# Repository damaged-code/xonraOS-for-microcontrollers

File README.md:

# xonraOS

**xonraOS** is a tiny phone-style operating system for an **ESP8266 (NodeMCU)** with a **128x64 OLED** and **two buttons**. It has a Home screen, a Wi-Fi clock, two games, Settings, and an **app Store** that downloads small JavaScript apps from your own server. Anyone can write an app in a few lines and publish it by copying a file.

> Status: made by a beginner as a learning project and tested on one NodeMCU (ESP-12E, CP2102) board. Issues and pull requests are welcome.

## What is in it

- **Home:** apps in a smooth scrolling grid.
- **Clock:** time and date from the internet (NTP), 12 or 24 hour.
- **Jump** and **Snake:** two games with high scores and sound.
- **Settings:** time format, brightness, seconds, animations, what the second button does, sound, and **Wi-Fi setup from your phone** (the board opens its own network and a web page).
- **Store:** browse category tiles, then app tiles, then an app's details. Hold to open a tile; on details, hold to get, update or remove the app. Installed apps appear on Home.
- **Apps are JavaScript** ([Elk](https://github.com/cesanta/elk) engine). They can draw, read the buttons and a knob, play beeps, fetch web pages and save a value. See [docs/APPS.md](docs/APPS.md).
- Apps are loaded into memory only while open, and many apps can be installed at once.

Sample apps in `server/apps/`: Counter, Stopwatch, Notes (scrolling text from your server), Knob Test, Bounce, Calculator.

The expanded catalog adds Countdown, Focus, Breathe, Dice, Reaction, Math Quiz, Scoreboard, Metronome, Morse, and Lane Dodge. See [the app pack guide](docs/APP-PACK.md) for controls and limitations. Firmware V2.0.3 lists up to 24 Store entries; up to eight apps can be installed at once.

V2.0.4 adds **Settings > Storage/Memory**: used/total and free app-file storage (LittleFS), live free RAM (heap), and installed app slots. Values are in KiB (1,024 bytes). Hold to refresh storage, tap to go back; D6 also goes back when configured as Back. Storage totals describe the filesystem partition, not the entire flash chip.

## Raspberry Pi

xonraOS also runs on a Raspberry Pi 3B with the same OLED and the same apps: see [pi/README.md](pi/README.md).

## Hardware

| Part | Connects to |
|---|---|
| ESP8266 NodeMCU (ESP-12E) | USB |
| 0.96" SSD1306 OLED, I2C address 0x3C | VCC to 3V3, GND to GND, SCL to D1, SDA to D2 |
| Main button | D7 and GND |
| Second button | D6 and GND |
| Buzzer (optional) | + to D8, - to GND |
| Potentiometer (optional) | left pin 3V3, middle pin A0, right pin GND |

Buttons use the internal pull-up, so no resistors are needed. A wiring diagram for a breadboard is in [docs/wiring.html](docs/wiring.html) (open it in a browser). An editable SVG copy for Figma or Inkscape is in [docs/wiring.svg](docs/wiring.svg).

## Controls

- **Main button (D7):** tap = next / action, hold 0.6 s = select, hold 1.5 s = back to Home.
- **Second button (D6):** set in Settings > D6 button: Off, Home, or Back (previous item, turn left, jump).

In the ESP8266 Store, a 1.5 s hold goes back one level (details → apps → categories → Home). From V2.0.7 / build 9, D6 in Back mode selects the previous tile or returns from details to the app grid; it stays in the Store during loading or on an empty catalog. D6 in Home mode still goes straight Home. Tiles page automatically as you tap through them. Details show the app's leading comment description, an image placeholder, and empty stars (no ratings are collected). Long tile names are shortened; open a tile to see its full catalog name. This layout is available in V2.0.6 / OTA build 8; the Pi Store retains its category list.

## Build and flash

1. Install the [Arduino IDE](https://www.arduino.cc/en/software) or Arduino CLI, and the **esp8266** board package (3.1.2 was used).
2. Install the libraries **Adafruit SSD1306**, **Adafruit GFX Library** (with Adafruit BusIO) and **elk** (2.2.0) from the Library Manager.
3. Copy `firmware/xonraOS/secrets.example.h` to `secrets.h` in the same folder and fill in your Wi-Fi name, password and app server address. (The ESP8266 supports 2.4 GHz Wi-Fi only.)
4. Edit `TIME_ZONE` near the top of `xonraOS.ino` if you are not in UTC+3.
5. Board: **NodeMCU 1.0 (ESP-12E Module)**. Compile and upload, for example:

```
arduino-cli compile --upload -p COM5 --fqbn esp8266:esp8266:nodemcuv2 firmware/xonraOS
```

If an upload fails with a write error, try again. If the board is not detected, install the CP210x USB driver.

## Update the firmware over Wi-Fi

Open **Settings > Firmware** on the board. It shows the installed build (for example `v2`) and the latest one on your app server. If a newer one exists, hold the main button to install it. The board downloads it, checks its signature, reboots and runs it. Do not unplug it while it says "Updating...".

Safety: the board only installs builds **signed with the maintainer's private key**; the matching public key is built into the firmware (`firmware/xonraOS/public.key`). A tampered or unsigned file is refused. Anyone with a USB cable can still flash any firmware.

For maintainers (publishing a release):
1. Raise `FW_VERSION` in `xonraOS.ino`.
2. Build: `arduino-cli compile --fqbn esp8266:esp8266:nodemcuv2 --output-dir build firmware/xonraOS`
3. Sign: `node tools/release-firmware.js build/xonraOS.ino.bin <path to private.key> release`
4. Copy `release/xonraos.bin` and `release/version.txt` to `firmware/` on your app server (so they are served at `/firmware/xonraos.bin` and `/firmware/version.txt`).

To run your own releases, make your own key pair (see the comments in `tools/release-firmware.js`), replace `public.key`, flash once over USB, and sign with your private key. Never commit `private.key`.

## Use the public app store

The quickest way to try the Store is the public one. In `secrets.h` set:

```
#define STORE_URL "http://35.174.38.92"
```

Browse the apps, with a live preview of each one, at **https://apps.xonra.cyou**. (The website uses `https://`; the board itself uses the plain `http://` address above because it cannot do `https://`.)

It serves whatever is in `server/` on the `main` branch of this repository (refreshed about every 10 minutes), so the apps there are the ones you see in the Store. To add an app, open a pull request that adds `server/apps/<id>.js` and a line in `server/manifest.txt`. Apps are reviewed before they are merged. The store is plain `http://` (the board cannot use `https://`), so install only apps you trust. It is a small hobby server and may go away; you can always host your own (next section).

## Run your own app server

```
cd server
python -m http.server 8266
```

Use the computer's LAN address as `STORE_URL` in `secrets.h`. Details: [server/README.md](server/README.md).

## Write an app

```js
//Hello|1|Hello
let n = 0;
let draw = function() {
  ctext(8, 1, 'Hello');
  ctext(24, 3, str(n));
  ctext(54, 1, 'Tap = +1');
};
let tap = function() { n = n + 1; };
```

Save it as `server/apps/hello.js`, add `hello|Hello|1|Tools` to `server/manifest.txt`, and install it from the Store. Read [docs/APPS.md](docs/APPS.md) first: the script engine has some bugs that fail silently, and there is a test harness (`tools/harness.c`) to check your app on your computer.

## Repository layout

```
firmware/xonraOS/   the OS (Arduino sketch)  - GPL-3.0
server/               app server files and sample apps - MIT
hardware/             open board design (draft) - CERN-OHL-S-2.0
pi/                   Raspberry Pi 3B version (same apps) - GPL-3.0
tools/harness.c       test an app on your computer
docs/                 app guide and wiring diagram
```

## License and credits

- The firmware and tools are under the **GNU GPL v3** (`LICENSE`), because they include the [Elk](https://github.com/cesanta/elk) JavaScript engine by Cesanta (AGPL/GPL). The sample apps and server files in `server/` are under the **MIT** license (`server/LICENSE`), so you can license your own apps as you like.
- Built on [Elk](https://github.com/cesanta/elk), the [ESP8266 Arduino core](https://github.com/esp8266/Arduino), and Adafruit's SSD1306, GFX and BusIO libraries.

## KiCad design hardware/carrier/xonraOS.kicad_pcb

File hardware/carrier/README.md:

# xonraOS carrier board v0.3 (the low-cost version)

A 2-layer, 60 × 88 mm board with the same outline, screen, buttons and side wheel as the v0.2 board, so it fits the
printed case in `../case`. The difference: instead of a factory-assembled ESP8266 + USB circuit, a ready-made
**Wemos D1 mini** is soldered flat onto it. Every part is through-hole or has big pads, so you can **order the bare
board (no assembly fee) and solder it yourself**.

Checked with KiCad's design-rule check: **0 unconnected pins, 0 errors** (only cosmetic silkscreen warnings).

> **Status: not built yet.** Measure your D1 mini before ordering (see "Check before ordering").

## Cost (rough, November 2026)

| Item | Where | Approx. |
|---|---|---|
| Carrier PCB, 5 pcs (`production/xonraOS-gerbers.zip`) | JLCPCB, no assembly | $2–4 |
| Wemos D1 mini (ESP8266, CH340) | AliExpress | about 8 SAR |
| 1.8" ST7735 TFT 128×160, SPI, 8-pin | AliExpress | about 12–15 SAR |
| 2 × 12 × 12 × 4.3 mm tactile buttons, 5 × 5 mm buzzer, 220 Ω resistor | AliExpress | about 5 SAR |
| Flat 16 mm thumbwheel potentiometer 10k | AliExpress | about 3–5 SAR |
| Case (`../case`) | JLC3DP, same order as the PCB | about 40 SAR |

Shipping is the biggest unknown: order the PCB and the case together, and all the small parts in one AliExpress order.

## Order the board

JLCPCB → "Add gerber file" → `production/xonraOS-gerbers.zip`. 2 layers, 1.6 mm, any colour. **Leave "PCB Assembly" off.**

## Solder it

1. **D1 mini:** push its male pin header through the D1 mini and the carrier, then **slide the black plastic spacer
   off** so the D1 mini lies flat (the parts under it drop into the cutout). USB to the left board edge. Solder both sides, trim.
2. **Screen (J2):** pin 1 at the top = VCC, then GND, CS, RESET, A0/DC, SDA, SCK, LED.
3. **Buttons** SW1 (main, D3) and SW2 (second, D6), **R1** 220 Ω, **buzzer LS1** (+ pad marked), **wheel RV1**.
4. Trim all solder legs on the back to about 1.5 mm so the board sits on the case posts.
5. Flash `firmware/xonraOS_TFT` as usual over the D1 mini's USB. No firmware changes are needed.

## Circuit

| D1 mini pin | Goes to |
|---|---|
| D5, D7 | TFT SCK, SDA (MOSI) |
| D1, D2 | TFT CS, A0/DC |
| RST | TFT RESET |
| D3 | main button to GND |
| D6 | second button to GND |
| D8 | 220 Ω, then buzzer to GND |
| A0 | wheel wiper (wheel ends on 3V3 and GND) |
| 3V3, G | TFT VCC and LED, wheel, ground pour |

## Check before ordering

- **D1 mini pin position:** the footprint assumes the 3V3/5V pins sit 5.6 mm from the USB end (typical). Measure yours.
- **Parts under the D1 mini** must fit inside the cutout (16.4 mm wide).
- **TFT pin order** as above (common red module). If yours differs, change the J2 pads in `make_board.py`.
- **Buzzer and wheel footprints** are generic (`../pcb/xonraOS.pretty`): compare with the parts you buy.

## Rebuild

From Git Bash: `sh build.sh` (KiCad 10, Freerouting 2.5 + Java 25), then
`"<KiCad>\bin\python.exe" export_jlc.py`. The script `make_board.py` holds all parts and nets.

License: CERN-OHL-S-2.0

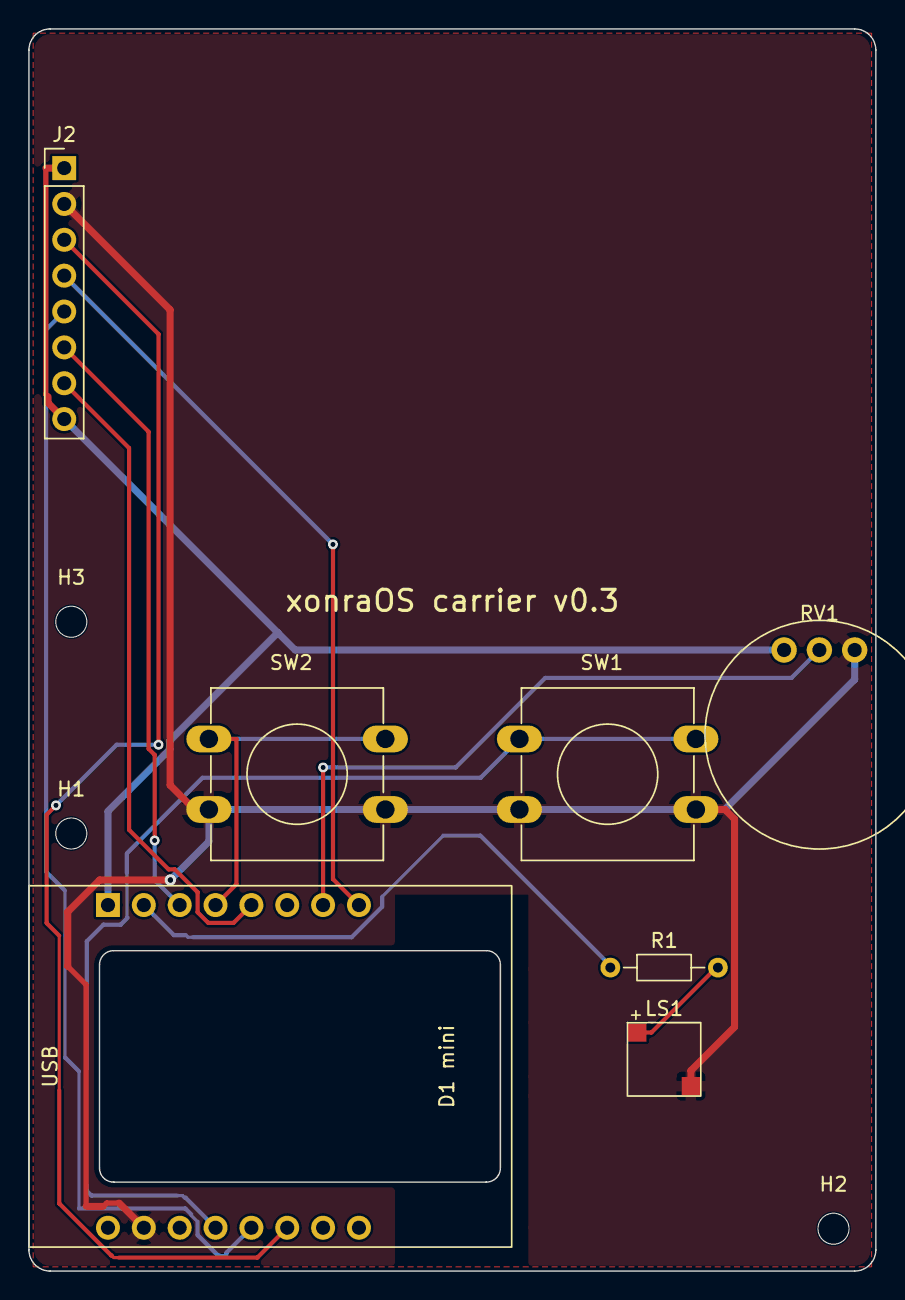
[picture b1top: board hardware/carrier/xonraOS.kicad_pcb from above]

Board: 2 copper layers, 60.0 x 88.0 mm, 10 parts (0 on the bottom side), 12 nets.

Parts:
H1, H2, H3: M2; MountingHole_2.2mm_M2
J2: TFT 1.8in ST7735; PinHeader_1x08_P2.54mm_Vertical
LS1: Buzzer 5x5; Buzzer_5x5_SMD
R1: 220R; R_Axial_DIN0204_L3.6mm_D1.6mm_P7.62mm_Horizontal
RV1: 10k thumbwheel; Thumbwheel_16mm
SW1: Main (D3); SW_PUSH-12mm
SW2: Second (D6); SW_PUSH-12mm
U1: Wemos D1 mini; WEMOS_D1_mini_flat

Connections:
+3V3: J2.1, J2.8, RV1.1, U1.3V3
BTN1: SW1.1, U1.D3
BTN2: SW2.1, U1.D6
BUZ: LS1.1, R1.2
BUZ_DRV: R1.1, U1.D8
GND: J2.2, LS1.2, RV1.3, SW1.2, SW2.2, U1.G
RST: J2.4, U1.RST
TFT_CS: J2.3, U1.D1
TFT_DC: J2.5, U1.D2
TFT_MOSI: J2.6, U1.D7
TFT_SCK: J2.7, U1.D5
WIPER: RV1.2, U1.A0

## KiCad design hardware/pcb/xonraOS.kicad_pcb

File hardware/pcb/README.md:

# xonraOS board v0.2 — KiCad PCB (1.8" colour TFT, portrait)

A 2-layer, 60 × 88 mm board that runs the TFT firmware (`firmware/xonraOS_TFT`) and fits the printed case in `../case`.
It was generated by scripts, routed with Freerouting, and checked with KiCad's design-rule check:
**0 unconnected pins, 0 electrical errors** (only cosmetic silkscreen warnings; see `drc-report.json`).

> **Status: not built yet.** The first boards may need small fixes. Before ordering, ask someone experienced to
> look at it (for example r/PrintedCircuitBoard), and check the parts below.

## Order it (JLCPCB)

Everything is in `production/`:

| File | Upload where |
|---|---|
| `xonraOS-gerbers.zip` | "Add gerber file". 2 layers, 1.6 mm, any colour (black looks premium). |
| `bom.csv` | "PCB Assembly" → BOM. Parts marked "by hand" are not assembled by JLCPCB. |
| `cpl.csv` | "PCB Assembly" → CPL (placement). |

In the assembly preview, **check the rotation of each part** (especially U1, U2, U3, the transistors and J1)
and rotate any that look wrong: the factory's part models do not always match KiCad's.

Solder these yourself afterwards (then trim all solder legs to about 1.5 mm so the board fits the thin case): the 1.8" TFT module (on J2, 8-pin header), the two low-profile 12 × 12 × 4.3 mm buttons (SW1, SW2),
the 5 × 5 mm buzzer (LS1) and the flat 16 mm thumbwheel potentiometer (RV1).

## What to check before ordering

- **TFT pin order (J2):** pin 1 at the top = VCC, then GND, CS, RESET, A0/DC, SDA, SCK, LED. This is the order on the
  common red 1.8" module; if yours differs, change the J2 pads in `make_board.py` and rebuild.
- **Buzzer (LS1) and thumbwheel (RV1)** use generic footprints in `xonraOS.pretty`: compare them with the datasheet of
  the parts you buy (pad positions, pin order: RV1 pin 1 = 3V3, 2 = wiper, 3 = GND).
- **LCSC part numbers** in `make_board.py` were picked from memory: confirm each is in stock at JLCPCB.

## Circuit summary

Pins match the TFT firmware: TFT SCK GPIO14, MOSI GPIO13, CS GPIO5, DC GPIO4, RESET = board reset; main button GPIO0
(also the flash button), second button GPIO12, buzzer GPIO15 through an S8050 transistor, thumbwheel on the ADC through a
220k/100k divider. USB-C → CH340C (powered at 3.3 V) with automatic reset/flash (two S8050s on DTR/RTS) → no buttons
needed to upload. AMS1117-3.3 regulator. The full net list is the `NETS` table in `make_board.py`.

## Rebuild it

Needs KiCad 10 and Java 25 + [Freerouting](https://github.com/freerouting/freerouting) 2.5.

```
"<KiCad>\bin\python.exe" make_board.py        # place parts, nets, outline, pours, keep-outs
"<KiCad>\bin\python.exe" route.py <java.exe> <freerouting.jar> 150
"<KiCad>\bin\kicad-cli.exe" pcb drc --refill-zones --save-board xonraOS.kicad_pcb
"<KiCad>\bin\python.exe" export_jlc.py        # production/ files
```

Part positions in `make_board.py` must stay in step with `../case/xonra-board-case.js` (buttons, wheel, USB-C, screen).

License: CERN-OHL-S-2.0 (see `../LICENSE`).

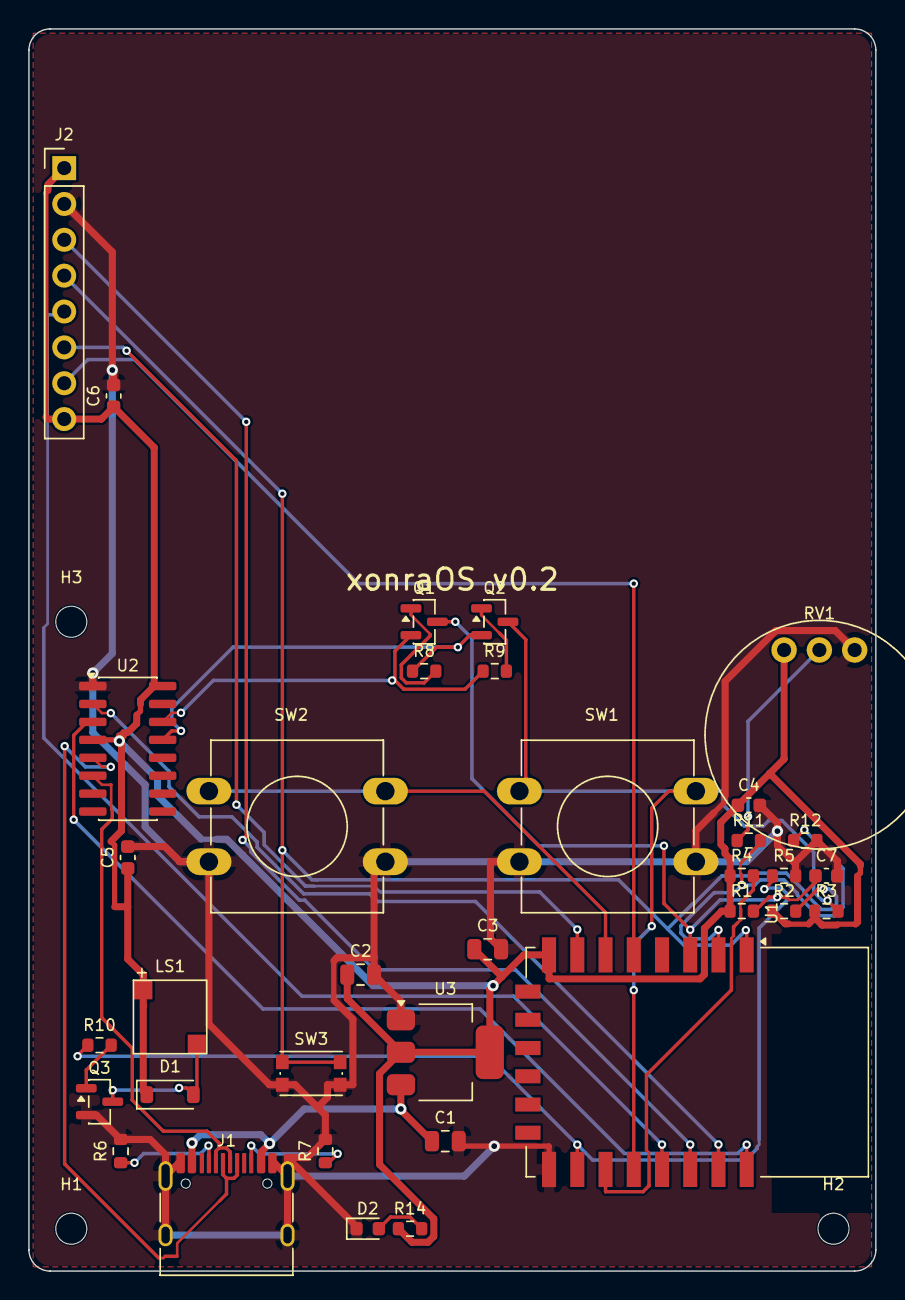
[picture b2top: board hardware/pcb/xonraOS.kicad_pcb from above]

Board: 2 copper layers, 60.0 x 88.0 mm, 38 parts (0 on the bottom side), 28 nets.

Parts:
C1, C2, C3: 10uF; C_0805_2012Metric
C4, C5, C6, C7: 100nF; C_0603_1608Metric
D1: 1N4148W; D_SOD-123
D2: LED; LED_0603_1608Metric
H1, H2, H3: M2; MountingHole_2.2mm_M2
J1: USB-C; USB_C_Receptacle_HRO_TYPE-C-31-M-12
J2: TFT 1.8in ST7735; PinHeader_1x08_P2.54mm_Vertical
LS1: Buzzer 5x5; Buzzer_5x5_SMD
Q1, Q2, Q3: S8050; SOT-23
R1, R2, R3, R4, R5, R8, R9: 10k; R_0603_1608Metric
R6, R7: 5.1k; R_0603_1608Metric
R10, R14: 1k; R_0603_1608Metric
R11: 220k; R_0603_1608Metric
R12: 100k; R_0603_1608Metric
RV1: 10k thumbwheel; Thumbwheel_16mm
SW1: Main (GPIO0); SW_PUSH-12mm
SW2: Second (GPIO12); SW_PUSH-12mm
SW3: Reset; SW_Push_1P1T_NO_CK_KMR2
U1: ESP-12F; ESP-12E
U2: CH340C; SOIC-16_3.9x9.9mm_P1.27mm
U3: AMS1117-3.3; SOT-223-3_TabPin2

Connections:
+3V3: C2.1, C3.1, C4.1, C5.1, C6.1, D1.1, J2.1, J2.8, LS1.1, R1.1, R2.1, R3.1, R4.1, R14.1, RV1.1, U1.8, U2.4, U2.16, U3.2
BTN2: SW2.1, U1.6
BUZ_N: D1.2, LS1.2, Q3.3
CC1: J1.A5, R6.1
CC2: J1.B5, R7.1
DTR: Q2.2, R8.1, U2.13
EN: C7.1, Q1.3, R1.2, U1.3
ESP_RX: U1.21, U2.2
ESP_TX: U1.22, U2.3
GND: C1.2, C2.2, C3.2, C4.2, C5.2, C6.2, C7.2, D2.1, J1.A1, J1.A12, J1.B1, J1.B12, J1.SH, J2.2, Q3.2, R5.2, R6.2, R7.2, R12.2, RV1.3, SW1.2, SW2.2, SW3.2, U1.15, U2.1, U3.1
GPIO0: Q2.3, R3.2, SW1.1, U1.18
GPIO2: R4.2, U1.17
GPIO15: R5.1, R10.1, U1.16
LED_A: D2.2, R14.2
Q1_B: Q1.1, R8.2
Q2_B: Q2.1, R9.2
Q3_B: Q3.1, R10.2
RST: J2.4, R2.2, SW3.1, U1.1
RTS: Q1.2, R9.1, U2.14
TFT_CS: J2.3, U1.20
TFT_DC: J2.5, U1.19
TFT_MOSI: J2.6, U1.7
TFT_SCK: J2.7, U1.5
TOUT: R11.2, R12.1, U1.2
USB_DM: J1.A7, J1.B7, U2.6
USB_DP: J1.A6, J1.B6, U2.5
VBUS: C1.1, J1.A4, J1.A9, J1.B4, J1.B9, U3.3
WIPER: R11.1, RV1.2

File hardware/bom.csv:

Comment,Designator,Footprint,LCSC,Qty,Assembly,Notes
ESP-12F,U1,ESP-12F module,C82891,1,machine,Verify LCSC number
CH340C,U2,SOP-16,C84681,1,machine,USB-serial with internal crystal; powered at 3.3 V
AMS1117-3.3,U3,SOT-223,C6186,1,machine,3.3 V regulator
USB-C 16-pin receptacle,J1,TYPE-C-31-M-12,C165948,1,machine,Verify footprint matches part
TFT header pads (8 x 2.54 mm holes),J2,PinHeader_1x08_P2.54mm,,0,hand,TFT module is soldered on with its own pins (2.5 mm spacer)
S8050 NPN,Q1 Q2 Q3,SOT-23,C2146,3,machine,Auto-reset (Q1 Q2) and buzzer driver (Q3)
1N4148W,D1,SOD-123,C81598,1,machine,Buzzer flyback diode
LED green,D2,0603,C72043,1,machine,Power LED
Magnetic buzzer 5x5 mm 3.6 V,LS1,MLT-5020,,1,machine,Passive buzzer driven by tone(); pick an LCSC 5x5 part
Tactile switch 12x12x4.3 mm low-profile (THT),SW1 SW2,SW_PUSH_12mm,,2,hand,Main (D7) and second (D6) under printed 14 mm caps (button-cap.stl)
Tactile switch small SMD,SW3 SW4,SMD 4x3 mm,C318884,2,machine,RESET and FLASH; inside the case (USB flashing resets automatically)
10k thumbwheel potentiometer flat 16 mm wheel,RV1,thumbwheel (check datasheet),,1,hand,Lies flat; wheel rim sticks out of the right side of the case
10k resistor,R1 R2 R3 R4 R5 R8 R9,0603,C25804,7,machine,
5.1k resistor,R6 R7,0603,C23186,2,machine,USB-C CC pull-downs
1k resistor,R10 R14,0603,C21190,2,machine,
220k resistor,R11,0603,C22961,1,machine,Knob divider top; verify number
100k resistor,R12,0603,C25803,1,machine,Knob divider bottom; verify number
10uF capacitor,C1 C2 C3,0805,C15850,3,machine,Regulator in/out and ESP bulk
100nF capacitor,C4 C5 C6 C7,0603,C14663,4,machine,Decoupling and EN delay
1.8 inch ST7735 TFT module 160x128 SPI,DISP1,module,,1,hand,Buy separately (common red 1.8in SPI module); measure before printing the case

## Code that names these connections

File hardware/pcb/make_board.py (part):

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    "U3":  ("Package_TO_SOT_SMD", "SOT-223-3_TabPin2", 29.5, 15.5, 0, "AMS1117-3.3", "C6186"),
    "J1":  ("Connector_USB", "USB_C_Receptacle_HRO_TYPE-C-31-M-12", 14, 3.2, 0, "USB-C", "C165948"),
    "J2":  ("Connector_PinHeader_2.54mm", "PinHeader_1x08_P2.54mm_Vertical", 2.5, 69.25, 0, "TFT 1.8in ST7735", ""),
    "SW1": ("Button_Switch_THT", "SW_PUSH-12mm", 41, 31.5, 0, "Main (GPIO0)", ""),
    "SW2": ("Button_Switch_THT", "SW_PUSH-12mm", 19, 31.5, 0, "Second (GPIO12)", ""),
    "SW3": ("Button_Switch_SMD", "SW_Push_1P1T_NO_CK_KMR2", 20, 14, 0, "Reset", "C72443"),
    "LS1": ("xonraOS", "Buzzer_5x5_SMD", 10, 18, 0, "Buzzer 5x5", ""),
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    "Q2_B": [("R9", "2"), ("Q2", "1")],
    "EN": [("U1", "3"), ("R1", "2"), ("C7", "1"), ("Q1", "3")],
    "RST": [("U1", "1"), ("R2", "2"), ("SW3", "1"), ("J2", "4")],
    "GPIO0": [("U1", "18"), ("R3", "2"), ("Q2", "3"), ("SW1", "1")],
    "GPIO2": [("U1", "17"), ("R4", "2")],
    "GPIO15": [("U1", "16"), ("R5", "1"), ("R10", "1")],
    "Q3_B": [("R10", "2"), ("Q3", "1")],
    "BUZ_N": [("Q3", "3"), ("LS1", "2"), ("D1", "2")],
    "TFT_CS": [("U1", "20"), ("J2", "3")],    # GPIO5
    "TFT_DC": [("U1", "19"), ("J2", "5")],    # GPIO4
    "TFT_MOSI": [("U1", "7"), ("J2", "6")],   # GPIO13
    "TFT_SCK": [("U1", "5"), ("J2", "7")],    # GPIO14
    "BTN2": [("U1", "6"), ("SW2", "1")],      # GPIO12
    "TOUT": [("U1", "2"), ("R11", "2"), ("R12", "1")],
    "WIPER": [("RV1", "2"), ("R11", "1")],
    "LED_A": [("R14", "2"), ("D2", "2")],
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

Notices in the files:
hardware/carrier/xonraOS.kicad_pcb:
github.com/damaged-code/xonraOS-for-microcontrollers  CERN-OHL-S-2.0
